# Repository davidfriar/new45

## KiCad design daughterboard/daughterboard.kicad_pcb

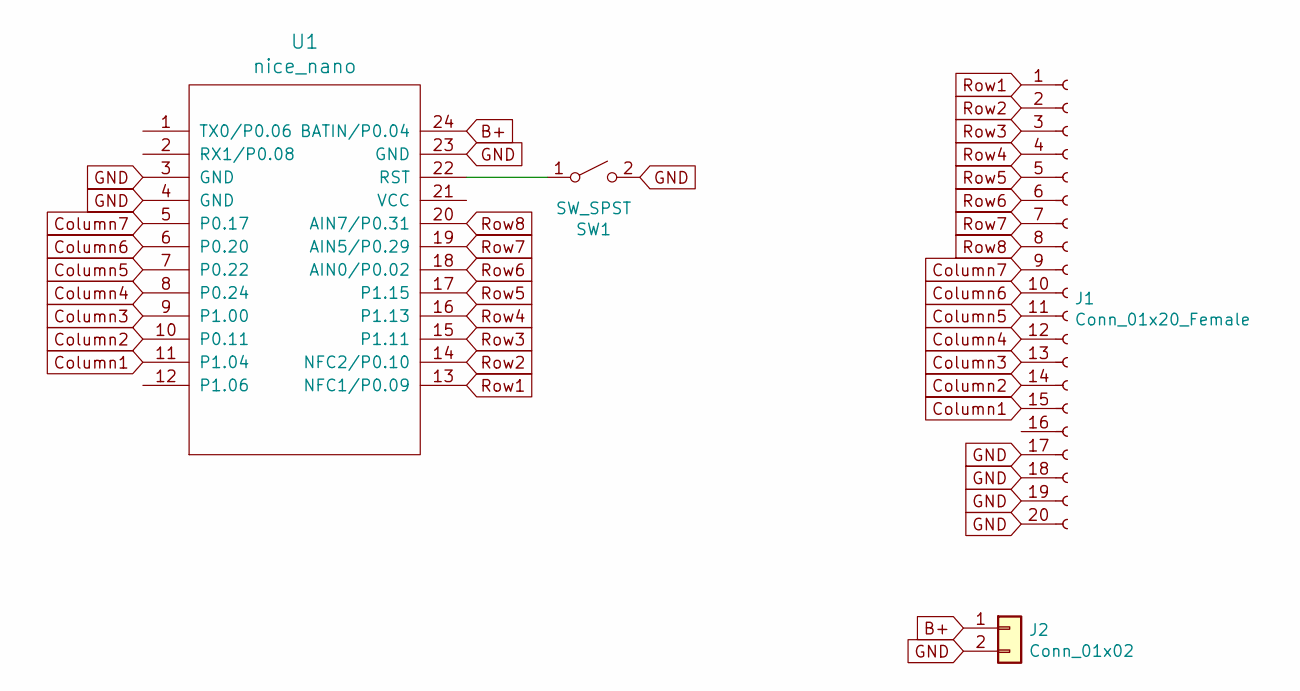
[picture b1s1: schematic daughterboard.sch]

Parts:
J1: Conn_01x20_Female; Molex2004850420
J2: Conn_01x02; JST_PH_S2B-PH-K_1x02_P2.00mm_Horizontal
SW1: SW_SPST; SW_Tactile_SPST_Angled_PTS645Vx83-2LFS
U1: nice_nano

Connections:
B+: J2.1, U1.24 (BATIN/P0.04)
Column1: J1.15, U1.11 (P1.04)
Column2: J1.14, U1.10 (P0.11)
Column3: J1.13, U1.9 (P1.00)
Column4: J1.12, U1.8 (P0.24)
Column5: J1.11, U1.7 (P0.22)
Column6: J1.10, U1.6 (P0.20)
Column7: J1.9, U1.5 (P0.17)
GND: J1.17, J1.18, J1.19, J1.20, J2.2, SW1.2 (B), U1.3 (GND), U1.4 (GND), U1.23 (GND)
unnamed: SW1.1 (A), U1.22 (RST)
Row1: J1.1, U1.13 (NFC1/P0.09)
Row2: J1.2, U1.14 (NFC2/P0.10)
Row3: J1.3, U1.15 (P1.11)
Row4: J1.4, U1.16 (P1.13)
Row5: J1.5, U1.17 (P1.15)
Row6: J1.6, U1.18 (AIN0/P0.02)
Row7: J1.7, U1.19 (AIN5/P0.29)
Row8: J1.8, U1.20 (AIN7/P0.31)

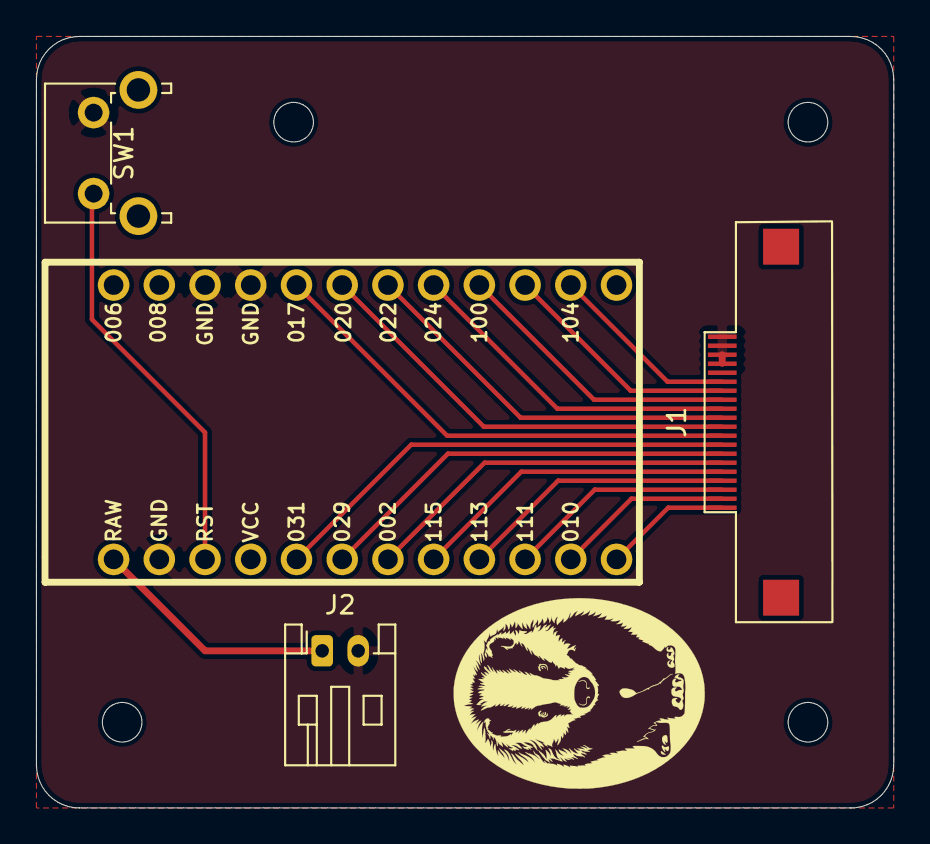
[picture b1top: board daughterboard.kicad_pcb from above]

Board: 2 copper layers, 47.6 x 42.9 mm, 4 parts (1 on the bottom side), 18 nets.

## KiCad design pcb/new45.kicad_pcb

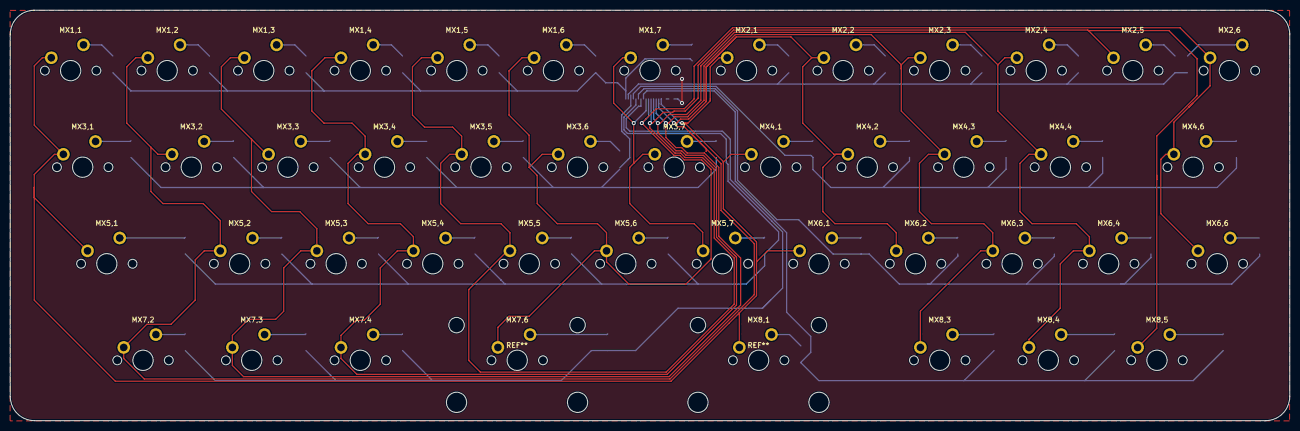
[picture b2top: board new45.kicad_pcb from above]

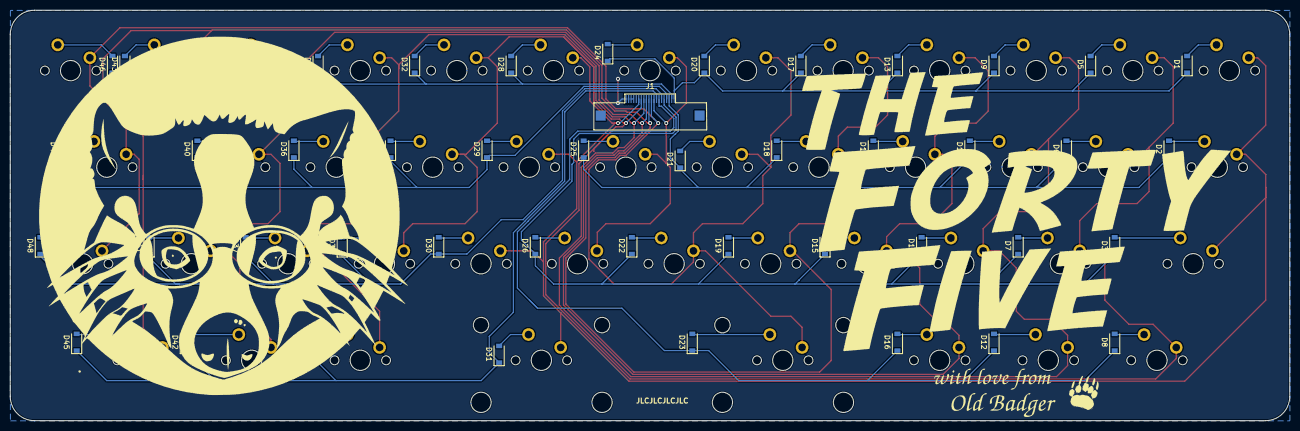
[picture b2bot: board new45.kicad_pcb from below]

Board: 2 copper layers, 252.4 x 81.0 mm, 91 parts (46 on the bottom side), 61 nets.

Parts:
D1, D2, D3, D5, D6, D7, D8, D9, D10, D11, D12, D13, D14, D15, D16, D17, D18, D19, D20, D21, D22, D23, D24, D25, D26, D28, D29, D30, D31, D32, D33, D34, D35, D36, D37, D38, D39, D40, D41, D42, D43, D45, D46, D47, D48: D_SOD-123
J1: Conn_01x20_Female; Molex2004850420
MX1,1, MX1,2, MX1,3, MX1,4, MX1,5, MX1,6, MX1,7, MX2,1, MX2,2, MX2,3, MX2,4, MX2,5, MX2,6, MX3,2, MX3,3, MX3,4, MX3,5, MX3,6, MX3,7, MX4,1, MX4,2, MX4,3, MX4,4, MX5,2, MX5,3, MX5,4, MX5,5, MX5,6, MX5,7, MX6,1, MX6,2, MX6,3, MX6,4, MX7,2, MX7,4, MX8,3, MX8,5: MX-NoLED; SW_Cherry_MX_PCB_1.00u
MX3,1, MX6,6, MX7,3, MX8,4: MX-NoLED; SW_Cherry_MX_PCB_1.25u
MX4,6, MX5,1: MX-NoLED; SW_Cherry_MX_PCB_1.75u
MX7,6: MX-NoLED; SW_Cherry_MX_PCB_2.25u
MX8,1: MX-NoLED; SW_Cherry_MX_PCB_2.75u

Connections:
Col1: J1.6, MX1,1.1, MX2,1.1, MX3,1.1, MX4,1.1, MX5,1.1, MX6,1.1, MX8,1.1
Col2: J1.7, MX1,2.1, MX2,2.1, MX3,2.1, MX4,2.1, MX5,2.1, MX6,2.1, MX7,2.1
Col3: J1.8, MX1,3.1, MX2,3.1, MX3,3.1, MX4,3.1, MX5,3.1, MX6,3.1, MX7,3.1, MX8,3.1
Col4: J1.9, MX1,4.1, MX2,4.1, MX3,4.1, MX4,4.1, MX5,4.1, MX6,4.1, MX7,4.1, MX8,4.1
Col5: J1.10, MX1,5.1, MX2,5.1, MX3,5.1, MX5,5.1, MX8,5.1
Col6: J1.11, MX1,6.1, MX2,6.1, MX3,6.1, MX4,6.1, MX5,6.1, MX6,6.1, MX7,6.1
Col7: J1.12, MX1,7.1, MX3,7.1, MX5,7.1
GND: J1.1, J1.2, J1.3, J1.4
unnamed: D1.2, MX1,1.2
unnamed: D2.2, MX3,1.2
unnamed: D3.2, MX5,1.2
unnamed: D5.2, MX1,2.2
unnamed: D6.2, MX3,2.2
unnamed: D7.2, MX5,2.2
unnamed: D8.2, MX7,2.2
unnamed: D9.2, MX1,3.2
unnamed: D10.2, MX3,3.2
unnamed: D11.2, MX5,3.2
unnamed: D12.2, MX7,3.2
unnamed: D13.2, MX1,4.2
unnamed: D14.2, MX3,4.2
unnamed: D15.2, MX5,4.2
unnamed: D16.2, MX7,4.2
unnamed: D17.2, MX1,5.2
unnamed: D18.2, MX3,5.2
unnamed: D19.2, MX5,5.2
unnamed: D20.2, MX1,6.2
unnamed: D21.2, MX3,6.2
unnamed: D22.2, MX5,6.2
unnamed: D23.2, MX7,6.2
unnamed: D24.2, MX1,7.2
unnamed: D25.2, MX3,7.2
unnamed: D26.2, MX5,7.2
unnamed: D28.2, MX2,1.2
unnamed: D29.2, MX4,1.2
unnamed: D30.2, MX6,1.2
unnamed: D31.2, MX8,1.2
unnamed: D32.2, MX2,2.2
unnamed: D33.2, MX4,2.2
unnamed: D34.2, MX6,2.2
unnamed: D35.2, MX2,3.2
unnamed: D36.2, MX4,3.2
unnamed: D37.2, MX6,3.2
unnamed: D38.2, MX8,3.2
unnamed: D39.2, MX2,4.2
unnamed: D40.2, MX4,4.2
unnamed: D41.2, MX6,4.2
unnamed: D42.2, MX8,4.2
unnamed: D43.2, MX2,5.2
unnamed: D45.2, MX8,5.2
unnamed: D46.2, MX2,6.2
unnamed: D47.2, MX4,6.2
unnamed: D48.2, MX6,6.2
Row1: D1.1, D5.1, D9.1, D13.1, D17.1, D20.1, D24.1, J1.20
Row2: D28.1, D32.1, D35.1, D39.1, D43.1, D46.1, J1.19
Row3: D2.1, D6.1, D10.1, D14.1, D18.1, D21.1, D25.1, J1.18
Row4: D29.1, D33.1, D36.1, D40.1, D47.1, J1.17
Row5: D3.1, D7.1, D11.1, D15.1, D19.1, D22.1, D26.1, J1.16
Row6: D30.1, D34.1, D37.1, D41.1, D48.1, J1.15
Row7: D8.1, D12.1, D16.1, D23.1, J1.14
Row8: D31.1, D38.1, D42.1, D45.1, J1.13

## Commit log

2021-06-05 case updates
2021-06-21 add daughterboard
2021-06-21 add artwork
2021-06-21 add gitignore
2021-06-21 add main pcb
